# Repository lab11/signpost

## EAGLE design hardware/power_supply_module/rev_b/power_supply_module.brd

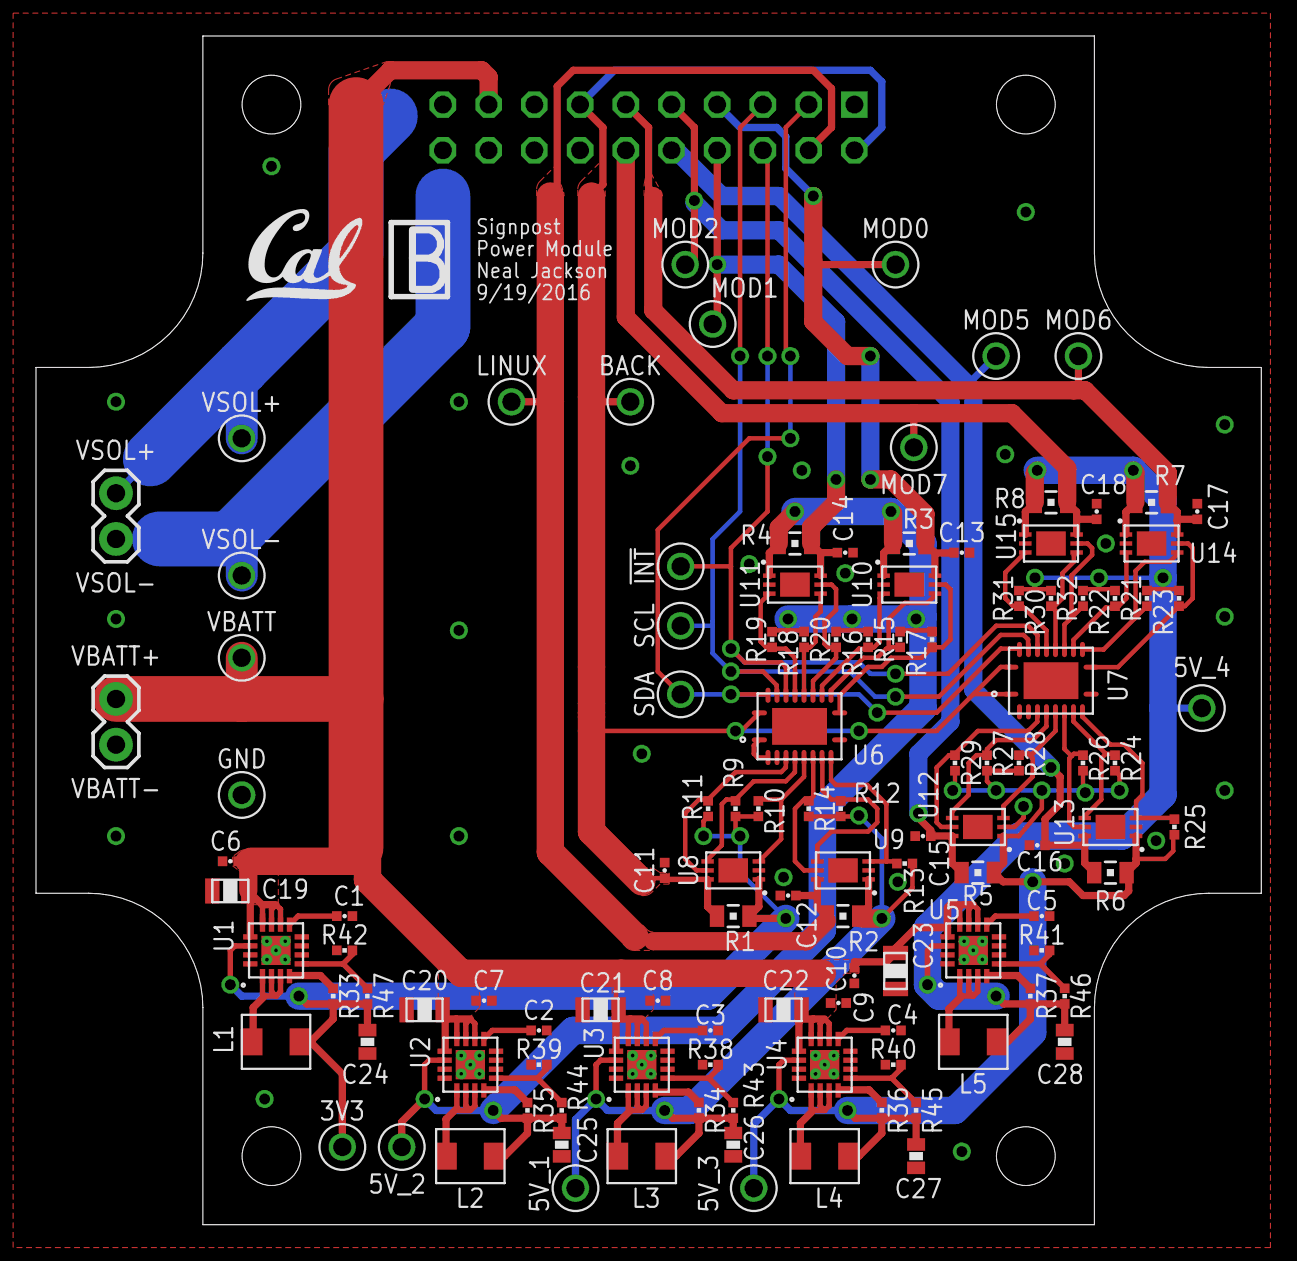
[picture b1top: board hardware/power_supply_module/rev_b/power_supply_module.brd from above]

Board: 2 copper layers, 68.1 x 66.0 mm, 119 parts (0 on the bottom side), 64 nets.

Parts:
3V3, 5V_1, 5V_2, 5V_3, 5V_4: TEST_POINT_0.040IN; TESTPOINT_0.040IN
!INT: TEST_POINT_0.040IN; TESTPOINT_0.040IN
BACK: TEST_POINT_0.040IN; TESTPOINT_0.040IN
C1, C2, C3, C4, C5: 3.3 nF; 0402_CAP
C6, C7, C8, C9, C10, C11, C12, C13, C14, C15, C16, C17, C18: 0.1 uF; 0402_CAP
C19, C20, C21, C22, C23: 10 uF; 0805_CAP
C24, C25, C26, C27, C28: 22 uF; 0603_CAP
GND: TEST_POINT_0.040IN; TESTPOINT_0.040IN
J1: MODULE_POWER
JP1, JP2: 1X02
L1, L2, L3, L4, L5: 2.2 uH; IHL-1212BZ-11
LINUX: TEST_POINT_0.040IN; TESTPOINT_0.040IN
MOD0, MOD1, MOD2, MOD5, MOD6, MOD7: TEST_POINT_0.040IN; TESTPOINT_0.040IN
R1, R2, R3, R4, R5, R6, R7, R8: 0.017 Ω; 0805_RES
R9, R10, R11, R12, R13, R14, R15, R16, R17, R18, R19, R20, R21, R22, R23, R24, R25, R26, R27, R28, R29, R30, R31, R32: 2 kΩ; 0402_RES
R33, R34, R35, R36, R37: 100 kΩ; 0402_RES
R38, R39, R40, R41: 130 kΩ; 0402_RES
R42: 240 kΩ; 0402_RES
R43, R44, R45, R46: 680 kΩ; 0402_RES
R47: 750 kΩ; 0402_RES
SCL: TEST_POINT_0.040IN; TESTPOINT_0.040IN
SDA: TEST_POINT_0.040IN; TESTPOINT_0.040IN
U1, U2, U3, U4, U5: TLV62130; TQFN-16/3MM
U6, U7: PCA9544AQFN-N20; QFN-N20
U8, U9, U10, U11, U12, U13, U14, U15: LTC2941; DFN-6-2MMX3MM
U$1: UCB_CAL_200MIL
VBATT: TEST_POINT_0.040IN; TESTPOINT_0.040IN
VSOL+: TEST_POINT_0.040IN; TESTPOINT_0.040IN
VSOL-: TEST_POINT_0.040IN; TESTPOINT_0.040IN

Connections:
3V3: 3V3.TESTPOINT, C24.2, L1.P$2, R1.2, R9.2, R10.2, R11.2, R33.2, R47.2, U1.14, U8.1
5V_1: 5V_1.TESTPOINT, C26.2, L3.P$2, R2.2, R12.2, R13.2, R14.2, R34.2, R43.2, U3.14, U9.1
5V_2: 5V_2.TESTPOINT, C25.2, L2.P$2, R3.2, R4.2, R15.2, R16.2, R17.2, R18.2, R19.2, R20.2, R35.2, R44.2, U2.14, U10.1, U11.1
5V_3: 5V_3.TESTPOINT, C27.2, L4.P$2, R5.2, R6.2, R24.2, R25.2, R26.2, R27.2, R28.2, R29.2, R36.2, R45.2, U4.14, U12.1, U13.1
5V_4: 5V_4.TESTPOINT, C28.2, L5.P$2, R7.2, R8.2, R21.2, R22.2, R23.2, R30.2, R31.2, R32.2, R37.2, R46.2, U5.14, U14.1, U15.1
!INT: !INT.TESTPOINT, J1.6, U6.17, U7.17
GND: C1.1, C2.1, C3.1, C4.1, C5.1, C6.2, C7.2, C8.2, C9.2, C10.2, C11.2, C12.2, C13.2, C14.2, C15.2, C16.2, C17.2, C18.2, C19.P$2, C20.P$2, C21.P$2, C22.P$2, C23.P$2, C24.1, C25.1, C26.1, C27.1, C28.1, GND.TESTPOINT, J1.1, J1.18, JP2.1, R38.1, R39.1, R40.1, R41.1, R42.1, U1.6, U1.7, U1.8, U1.15, U1.16, U1.GND, U2.6, U2.7, U2.8, U2.15, U2.16, U2.GND, U3.6, U3.7, U3.8, U3.15, U3.16, U3.GND, U4.6, U4.7, U4.8, U4.15, U4.16, U4.GND, U5.6, U5.7, U5.8, U5.15, U5.16, U5.GND, U6.1, U6.2, U6.3, U6.10, U7.2, U7.3, U7.10, U8.2, U9.2, U10.2, U11.2, U12.2, U13.2, U14.2, U15.2
unnamed: C2.2, U2.9
unnamed: L2.P$1, U2.1, U2.2, U2.3
unnamed: R35.1, U2.4
unnamed: R39.2, R44.1, U2.5
unnamed: C3.2, U3.9
unnamed: L3.P$1, U3.1, U3.2, U3.3
unnamed: R34.1, U3.4
unnamed: C4.2, U4.9
unnamed: R38.2, R43.1, U3.5
unnamed: L4.P$1, U4.1, U4.2, U4.3
unnamed: R36.1, U4.4
unnamed: R40.2, R45.1, U4.5
unnamed: C5.2, U5.9
unnamed: L5.P$1, U5.1, U5.2, U5.3
unnamed: R37.1, U5.4
unnamed: R41.2, R46.1, U5.5
unnamed: R27.1, U7.5, U12.4
unnamed: R28.1, U7.6, U12.3
unnamed: R21.1, U7.12, U14.4
unnamed: R22.1, U7.13, U14.3
unnamed: R23.1, U7.11, U14.5
unnamed: R30.1, U7.15, U15.4
unnamed: R31.1, U7.16, U15.3
unnamed: R9.1, U6.5, U8.4
unnamed: R32.1, U7.14, U15.5
unnamed: R10.1, U6.6, U8.3
unnamed: R29.1, U7.4, U12.5
unnamed: R24.1, U7.8, U13.4
unnamed: R25.1, U7.9, U13.3
unnamed: R26.1, U7.7, U13.5
unnamed: R15.1, U6.12, U10.4
unnamed: R16.1, U6.13, U10.3
unnamed: R17.1, U6.11, U10.5
unnamed: R18.1, U6.15, U11.4
unnamed: R19.1, U6.16, U11.3
unnamed: R20.1, U6.14, U11.5
unnamed: C1.2, U1.9
unnamed: L1.P$1, U1.1, U1.2, U1.3
unnamed: R33.1, U1.4
unnamed: R42.2, R47.1, U1.5
unnamed: R11.1, U6.4, U8.5
unnamed: R12.1, U6.8, U9.4
unnamed: R13.1, U6.9, U9.3
unnamed: R14.1, U6.7, U9.5
SCL: J1.5, SCL.TESTPOINT, U6.18, U7.18
SDA: J1.3, SDA.TESTPOINT, U6.19, U7.19
VBATT: C6.1, C7.1, C8.1, C9.1, C10.1, C19.P$1, C20.P$1, C21.P$1, C22.P$1, C23.P$1, J1.17, JP2.2, U1.10, U1.11, U1.12, U1.13, U2.10, U2.11, U2.12, U2.13, U3.10, U3.11, U3.12, U3.13, U4.10, U4.11, U4.12, U4.13, U5.10, U5.11, U5.12, U5.13, VBATT.TESTPOINT
VCC_BACKPLANE: BACK.TESTPOINT, C11.1, J1.2, J1.13, R1.1, U6.20, U7.1, U7.20, U8.6
VCC_LINUX: C12.1, J1.4, LINUX.TESTPOINT, R2.1, U9.6
VCC_MOD0: C13.1, J1.7, MOD0.TESTPOINT, R3.1, U10.6
VCC_MOD1: C14.1, J1.8, MOD1.TESTPOINT, R4.1, U11.6
VCC_MOD2: C15.1, J1.9, MOD2.TESTPOINT, R5.1, U12.6
VCC_MOD5: C16.1, J1.10, MOD5.TESTPOINT, R6.1, U13.6
VCC_MOD6: C17.1, J1.11, MOD6.TESTPOINT, R7.1, U14.6
VCC_MOD7: C18.1, J1.12, MOD7.TESTPOINT, R8.1, U15.6
VSOL+: J1.19, JP1.2, VSOL+.TESTPOINT
VSOL-: J1.20, JP1.1, VSOL-.TESTPOINT

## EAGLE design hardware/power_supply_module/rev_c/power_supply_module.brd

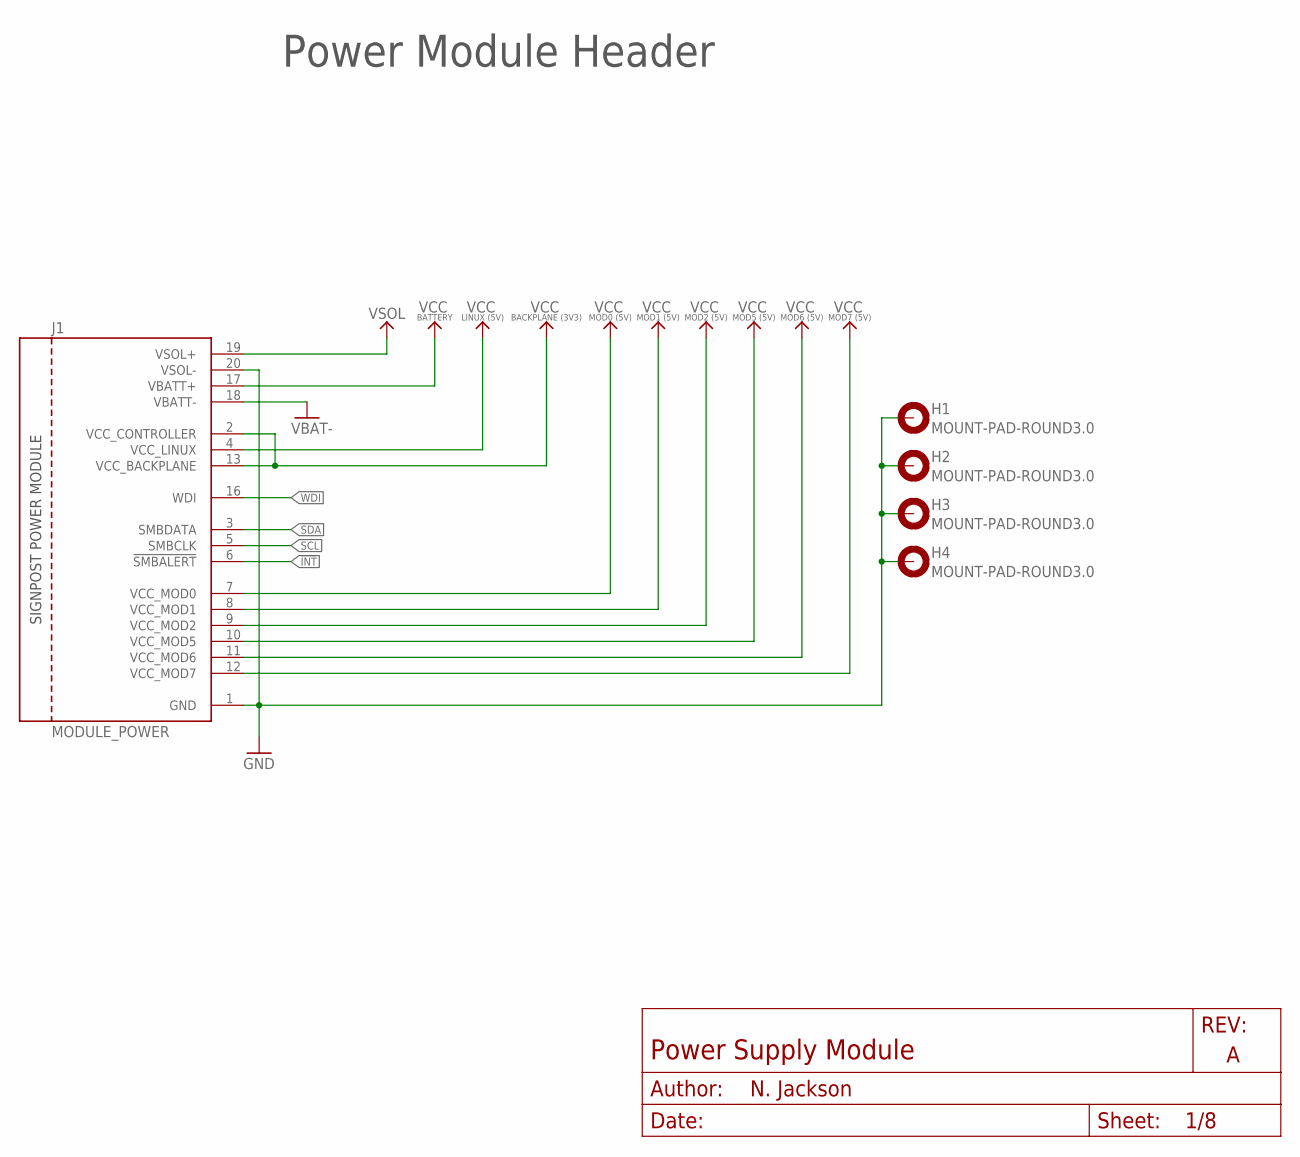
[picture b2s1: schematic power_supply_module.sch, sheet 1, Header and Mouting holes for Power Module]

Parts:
H1, H2, H3, H4: MOUNT-PAD-ROUND3.0; 3,0-PAD
J1: MODULE_POWER

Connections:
!INT: J1.6 (!SMBALERT); also elsewhere on the board
GND: H1.B3,0, H2.B3,0, H3.B3,0, H4.B3,0, J1.1 (GND), J1.20 (VSOL-); also elsewhere on the board
SCL: J1.5 (SMBCLK); also elsewhere on the board
SDA: J1.3 (SMBDATA); also elsewhere on the board
VBAT+: J1.17 (VBATT+); also elsewhere on the board
VBAT-: J1.18 (VBATT-); also elsewhere on the board
VCC_BACKPLANE: J1.2 (VCC_CONTROLLER), J1.13 (VCC_BACKPLANE); also elsewhere on the board
VCC_LINUX: J1.4 (VCC_LINUX); also elsewhere on the board
VCC_MOD0: J1.7 (VCC_MOD0); also elsewhere on the board
VCC_MOD1: J1.8 (VCC_MOD1); also elsewhere on the board
VCC_MOD2: J1.9 (VCC_MOD2); also elsewhere on the board
VCC_MOD5: J1.10 (VCC_MOD5); also elsewhere on the board
VCC_MOD6: J1.11 (VCC_MOD6); also elsewhere on the board
VCC_MOD7: J1.12 (VCC_MOD7); also elsewhere on the board
VSOL+: J1.19 (VSOL+); also elsewhere on the board
WDI: J1.16 (WDI); also elsewhere on the board

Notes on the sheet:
Power Module Header

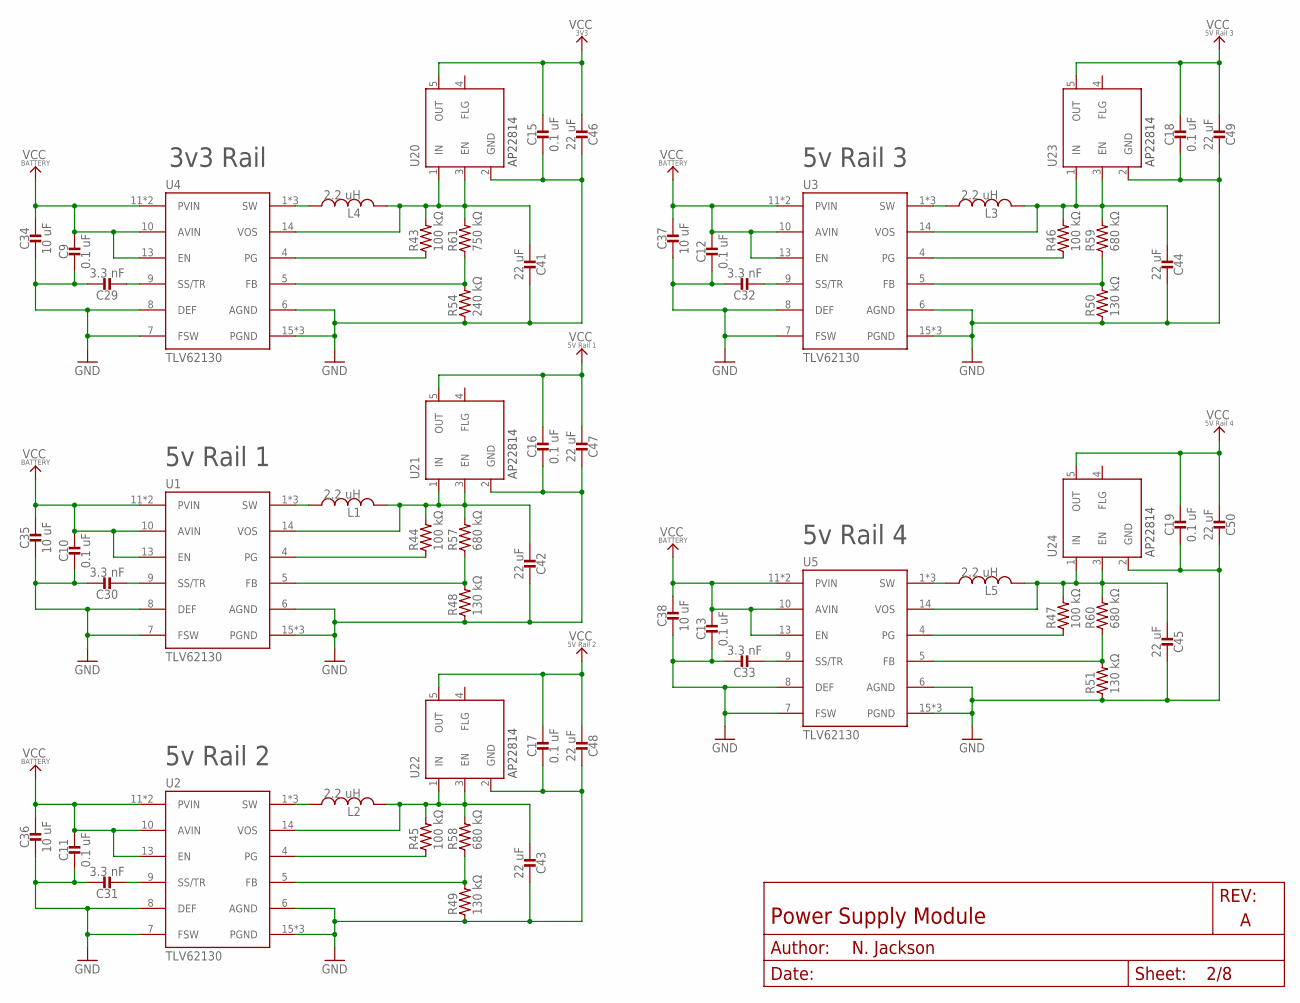
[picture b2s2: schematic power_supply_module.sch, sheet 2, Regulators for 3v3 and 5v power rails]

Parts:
C9, C10, C11, C12, C13, C15, C16, C17, C18, C19: 0.1 uF; 0402_CAP; DIGIKEY 490-5920-1-ND
C29, C30, C31, C32, C33: 3.3 nF; 0402_CAP; DIGIKEY 490-3248-1-ND
C34, C35, C36, C37, C38: 10 uF; 0805_CAP; DIGIKEY 490-5523-1-ND
C41, C42, C43, C44, C45, C46, C47, C48, C49, C50: 22 uF; 0603_CAP; DIGIKEY 1276-1193-1-ND
L1, L2, L3, L4, L5: 2.2 uH; IHL-1212BZ-11
R43, R44, R45, R46, R47: 100 kΩ; 0402_RES; DIGIKEY P100KJCT-ND
R48, R49, R50, R51: 130 kΩ; 0402_RES; DIGIKEY P130KLCT-ND
R54: 240 kΩ; 0402_RES; DIGIKEY P240JCT-ND
R57, R58, R59, R60: 680 kΩ; 0402_RES; DIGIKEY P680KLCT-ND
R61: 750 kΩ; 0402_RES; DIGIKEY P750KJCT-ND
U1, U2, U3, U4, U5: TLV62130; TQFN-16/3MM
U20, U21, U22, U23, U24: AP22814; U-DFN2020-6

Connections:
3V3ROUT: C41.2, L4.P$2 (2), R43.2, R61.2, U4.14 (VOS), U20.1 (IN), U20.3 (EN)
5V_1ROUT: C42.2, L1.P$2 (2), R44.2, R57.2, U1.14 (VOS), U21.1 (IN), U21.3 (EN)
5V_2ROUT: C43.2, L2.P$2 (2), R45.2, R58.2, U2.14 (VOS), U22.1 (IN), U22.3 (EN)
5V_3ROUT: C44.2, L3.P$2 (2), R46.2, R59.2, U3.14 (VOS), U23.1 (IN), U23.3 (EN)
5V_4ROUT: C45.2, L5.P$2 (2), R47.2, R60.2, U5.14 (VOS), U24.1 (IN), U24.3 (EN)
GND: C9.2, C10.2, C11.2, C12.2, C13.2, C15.2, C16.2, C17.2, C18.2, C19.2, C29.1, C30.1, C31.1, C32.1, C33.1, C34.P$2 (2), C35.P$2 (2), C36.P$2 (2), C37.P$2 (2), C38.P$2 (2), C41.1, C42.1, C43.1, C44.1, C45.1, C46.1, C47.1, C48.1, C49.1, C50.1, R48.1, R49.1, R50.1, R51.1, R54.1, U1.6 (AGND), U1.7 (FSW), U1.8 (DEF), U1.15 (PGND), U1.16 (PGND), U1.GND, U2.6 (AGND), U2.7 (FSW), U2.8 (DEF), U2.15 (PGND), U2.16 (PGND), U2.GND, U3.6 (AGND), U3.7 (FSW), U3.8 (DEF), U3.15 (PGND), U3.16 (PGND), U3.GND, U4.6 (AGND), U4.7 (FSW), U4.8 (DEF), U4.15 (PGND), U4.16 (PGND), U4.GND, U5.6 (AGND), U5.7 (FSW), U5.8 (DEF), U5.15 (PGND), U5.16 (PGND), U5.GND, U20.2 (GND), U21.2 (GND), U22.2 (GND), U23.2 (GND), U24.2 (GND); also elsewhere on the board
unnamed: L4.P$1 (1), U4.1 (SW), U4.2 (SW), U4.3 (SW)
unnamed: C30.2, U1.9 (SS/TR)
unnamed: R44.1, U1.4 (PG)
unnamed: R48.2, R57.1, U1.5 (FB)
unnamed: C31.2, U2.9 (SS/TR)
unnamed: L2.P$1 (1), U2.1 (SW), U2.2 (SW), U2.3 (SW)
unnamed: R45.1, U2.4 (PG)
unnamed: R49.2, R58.1, U2.5 (FB)
unnamed: C29.2, U4.9 (SS/TR)
unnamed: L1.P$1 (1), U1.1 (SW), U1.2 (SW), U1.3 (SW)
unnamed: C32.2, U3.9 (SS/TR)
unnamed: R43.1, U4.4 (PG)
unnamed: R54.2, R61.1, U4.5 (FB)
unnamed: L3.P$1 (1), U3.1 (SW), U3.2 (SW), U3.3 (SW)
unnamed: R46.1, U3.4 (PG)
unnamed: R50.2, R59.1, U3.5 (FB)
unnamed: C33.2, U5.9 (SS/TR)
unnamed: L5.P$1 (1), U5.1 (SW), U5.2 (SW), U5.3 (SW)
unnamed: R47.1, U5.4 (PG)
unnamed: R51.2, R60.1, U5.5 (FB)
VBAT+: C9.1, C10.1, C11.1, C12.1, C13.1, C34.P$1 (1), C35.P$1 (1), C36.P$1 (1), C37.P$1 (1), C38.P$1 (1), U1.10 (AVIN), U1.11 (PVIN), U1.12 (PVIN), U1.13 (EN), U2.10 (AVIN), U2.11 (PVIN), U2.12 (PVIN), U2.13 (EN), U3.10 (AVIN), U3.11 (PVIN), U3.12 (PVIN), U3.13 (EN), U4.10 (AVIN), U4.11 (PVIN), U4.12 (PVIN), U4.13 (EN), U5.10 (AVIN), U5.11 (PVIN), U5.12 (PVIN), U5.13 (EN); also elsewhere on the board
VCC_3V3: C15.1, C46.2, U20.5 (OUT); also elsewhere on the board
VCC_5V_1: C16.1, C47.2, U21.5 (OUT); also elsewhere on the board
VCC_5V_2: C17.1, C48.2, U22.5 (OUT); also elsewhere on the board
VCC_5V_3: C18.1, C49.2, U23.5 (OUT); also elsewhere on the board
VCC_5V_4: C19.1, C50.2, U24.5 (OUT); also elsewhere on the board

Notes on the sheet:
3v3 Rail
5v Rail 1
5v Rail 2
5v Rail 4
5v Rail 3

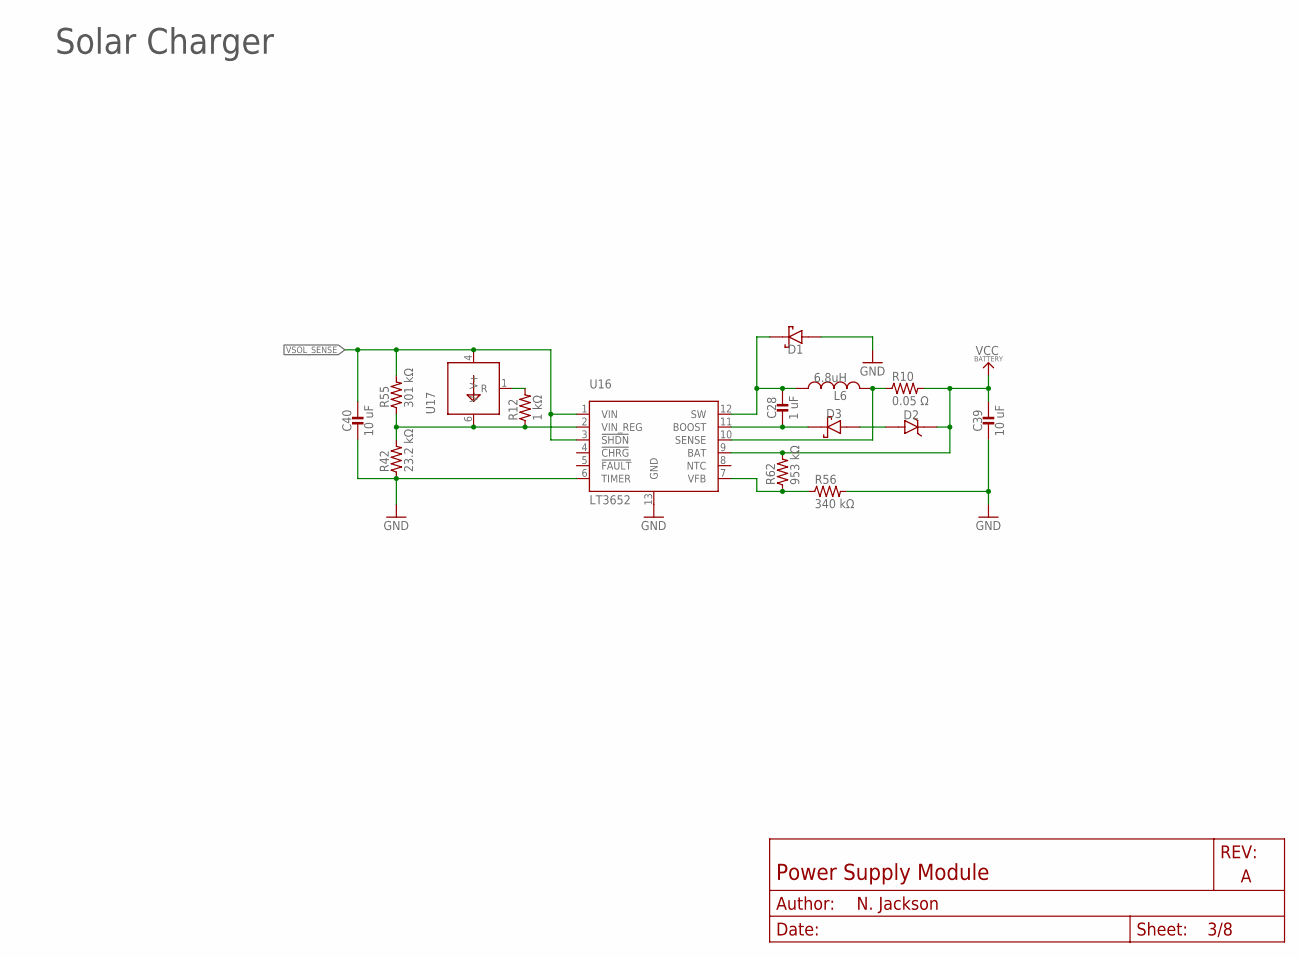
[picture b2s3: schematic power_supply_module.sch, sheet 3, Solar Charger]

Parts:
C28: 1 uF; 0603_CAP; DIGIKEY 490-3890-1-ND
C39, C40: 10 uF; 0805_CAP; DIGIKEY 490-5523-1-ND
D1: DIODE_SCHOTTKYSOT-23F; SOT-23F; DIGIKEY CMPSH1-4 CT-ND
D2: DIODE_ZENERSOT323; SOD323; DIGIKEY 1727-5151-1-ND
D3: DIODE_SCHOTTKYSOT-23F; SOT-23F; DIGIKEY CMDSH2-4L CT-ND
L6: 6.8uH; IHL-2525CZ; DIGIKEY 541-2582-1-ND
R10: 0.05 Ω; 0805_RES; DIGIKEY WSLPB-.05CT-ND
R12: 1 kΩ; 0402_RES; DIGIKEY P1.0KJCT-ND
R42: 23.2 kΩ; 0402_RES; DIGIKEY 311-2257-1-ND
R55: 301 kΩ; 0402_RES; DIGIKEY P301KLCT-ND
R56: 340 kΩ; 0402_RES; DIGIKEY P340KLCT-ND
R62: 953 kΩ; 0402_RES; DIGIKEY P953KLCT-ND
U16: LT3652; DFN-12/3MM
U17: LM234; SOIC-8

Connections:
BOOST: C28.2, D3.P$3 (CATHODE), U16.11 (BOOST)
GND: C39.P$2 (2), C40.P$2 (2), D1.P$1 (ANODE), R42.1, R56.2, U16.6 (TIMER), U16.13 (GND); also elsewhere on the board
unnamed: D2.P$2 (ANODE), D3.P$1 (ANODE)
unnamed: R12.2, U17.1 (R)
SENSE: L6.P$2 (2), R10.1, U16.10 (SENSE)
SW: C28.1, D1.P$3 (CATHODE), L6.P$1 (1), U16.12 (SW)
VBAT+: C39.P$1 (1), D2.P$1 (CATHODE), R10.2, R62.2, U16.9 (BAT); also elsewhere on the board
VFB: R56.1, R62.1, U16.7 (VFB)
VINREG: R12.1, R42.2, R55.1, U16.2 (VIN_REG), U17.6 (V-)
VSOL_SENSE: C40.P$1 (1), R55.2, U16.1 (VIN), U16.3 (!SHDN), U17.4 (V+); also elsewhere on the board

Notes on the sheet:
Solar Charger

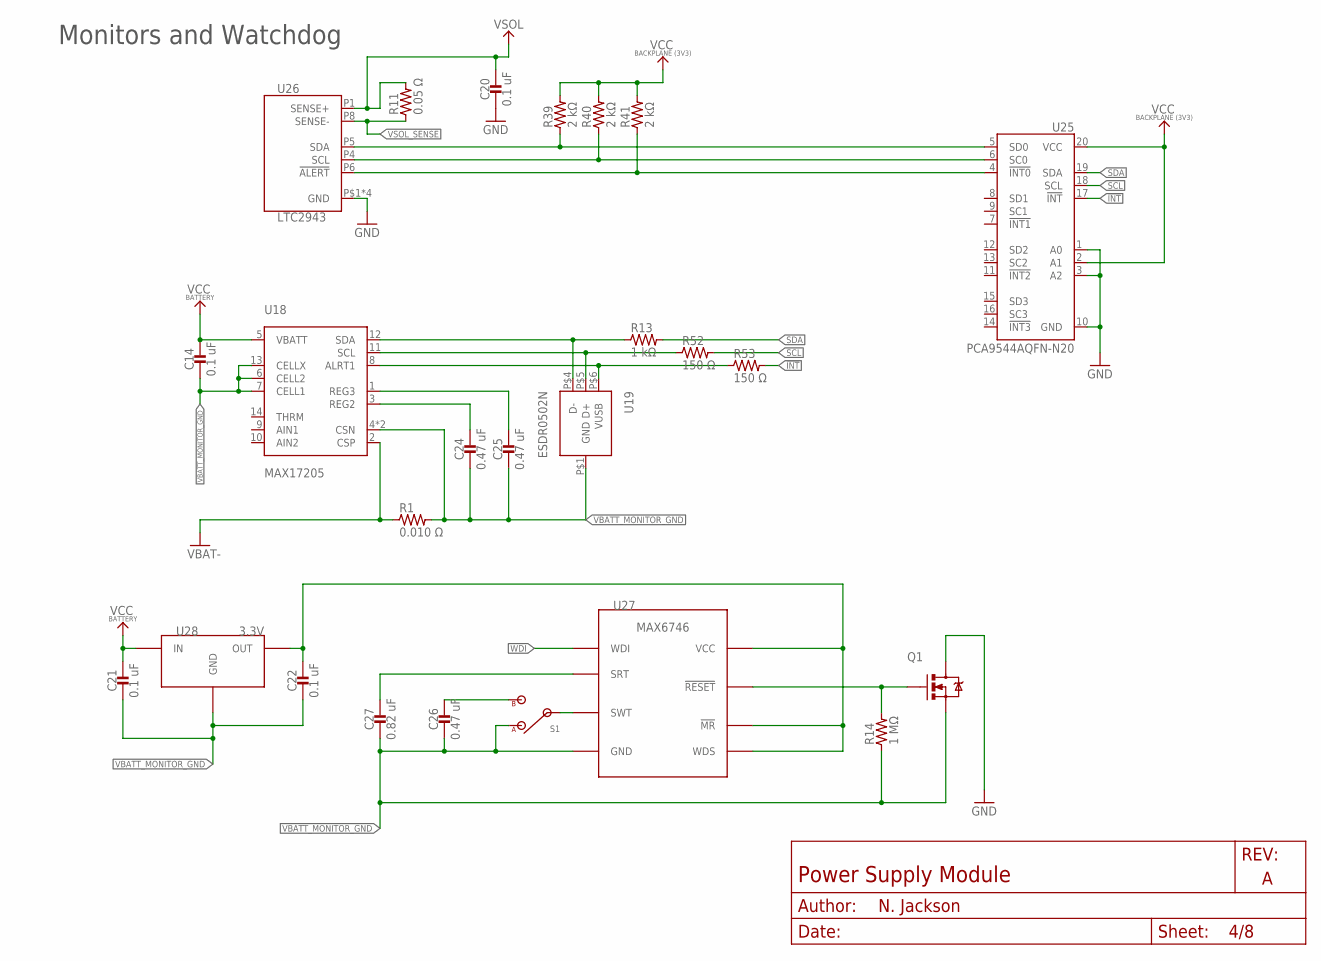
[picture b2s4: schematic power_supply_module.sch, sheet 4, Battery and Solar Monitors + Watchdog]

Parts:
C14, C20, C21, C22: 0.1 uF; 0402_CAP; DIGIKEY 490-5920-1-ND
C24, C25, C26: 0.47 uF; 0402_CAP; DIGIKEY 490-3266-1-ND
C27: 0.82 uF; 0402_CAP; DIGIKEY 490-10440-1-ND
Q1: MOSFET-NCHANNELFDD8580; DPAK; DIGIKEY NTD4965NT4GOSCT-ND
R1: 0.010 Ω; 0805_RES; DIGIKEY WSLPB-.01CT-ND
R11: 0.05 Ω; 0805_RES; DIGIKEY WSLPB-.05CT-ND
R13: 1 kΩ; 0402_RES; DIGIKEY P1.0KJCT-ND
R14: 1 MΩ; 0402_RES; DIGIKEY P1.00MLCT-ND
R39, R40, R41: 2 kΩ; 0402_RES; DIGIKEY P2.00KLCT-ND
R52, R53: 150 Ω; 0402_RES; DIGIKEY P150LCT-ND
S1: TE_SSA12/SPDT
U18: MAX17205; 14-TDFN
U19: ESDR0502N; UDFN-6
U25: PCA9544AQFN-N20; QFN-N20
U26: LTC2943; DFN-8
U27: MAX6746; SOT-23-8
U28: 3.3V; SOT-23

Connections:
!INT: R53.2, U25.17 (!INT); also elsewhere on the board
GND: C20.2, Q1.4 (D), U25.1 (A0), U25.3 (A2), U25.10 (GND), U26.P2 (GND), U26.P3 (GND), U26.P7 (GND), U26.P$1 (GND); also elsewhere on the board
unnamed: C27.1, U27.3 (SRT)
unnamed: R13.1, U18.12 (SDA), U19.P$4 (D-)
unnamed: C26.1, S1.2 (B)
unnamed: R52.1, U18.11 (SCL), U19.P$5 (D+)
unnamed: C24.1, U18.3 (REG2)
unnamed: R53.1, U18.8 (ALRT1), U19.P$6 (VUSB)
unnamed: C25.1, U18.1 (REG3)
unnamed: S1.IN, U27.2 (SWT)
unnamed: Q1.1 (G), R14.2, U27.7 (!RESET)
unnamed: C22.1, U27.1 (!MR), U27.5 (WDS), U27.8 (VCC), U28.1 (OUT)
unnamed: R41.1, U25.4 (!INT0), U26.P6 (!ALERT)
unnamed: R40.1, U25.6 (SC0), U26.P4 (SCL)
unnamed: R39.1, U25.5 (SD0), U26.P5 (SDA)
SCL: R52.2, U25.18 (SCL); also elsewhere on the board
SDA: R13.2, U25.19 (SDA); also elsewhere on the board
VBAT+: C14.1, C21.1, U18.5 (VBATT), U28.2 (IN); also elsewhere on the board
VBAT-: R1.1, U18.2 (CSP); also elsewhere on the board
VBATT_MONITOR_GND: C14.2, C21.2, C22.2, C24.2, C25.2, C26.2, C27.2, Q1.3 (S), R1.2, R14.1, S1.1 (A), U18.4 (CSN), U18.6 (CELL2), U18.7 (CELL1), U18.13 (CELLX), U18.15 (CSN), U19.P$1 (GND), U27.4 (GND), U28.3 (GND); also elsewhere on the board
VCC_BACKPLANE: R39.2, R40.2, R41.2, U25.2 (A1), U25.20 (VCC); also elsewhere on the board
VSOL+: C20.1, R11.2, U26.P1 (SENSE+); also elsewhere on the board
VSOL_SENSE: R11.1, U26.P8 (SENSE-); also elsewhere on the board
WDI: U27.6 (WDI); also elsewhere on the board

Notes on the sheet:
Monitors and Watchdog

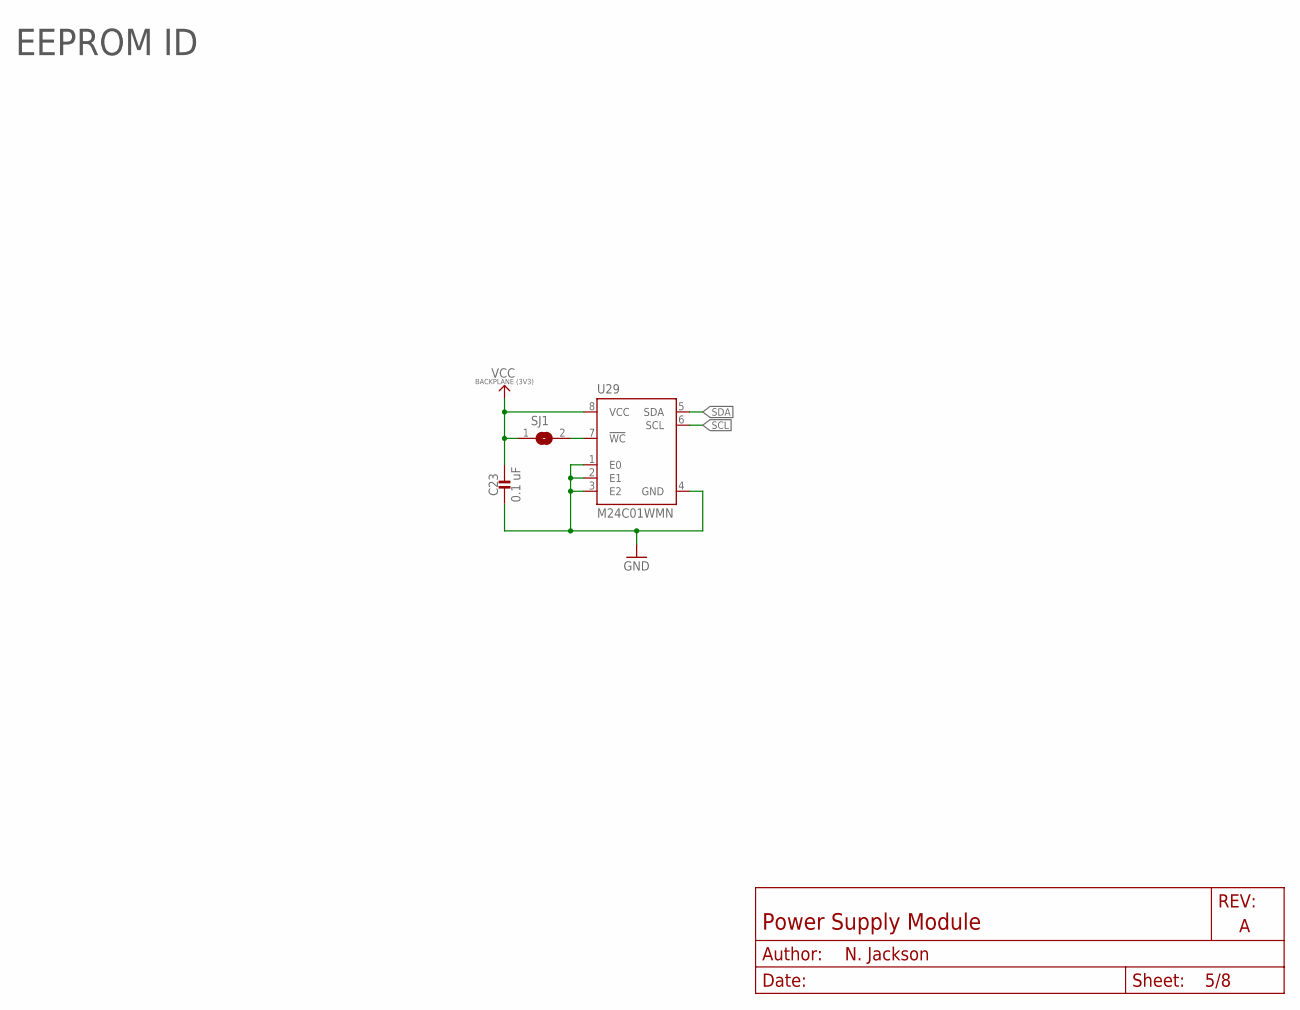
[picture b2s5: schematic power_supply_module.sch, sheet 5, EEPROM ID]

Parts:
C23: 0.1 uF; 0402_CAP; DIGIKEY 490-5920-1-ND
SJ1: SJ
U29: M24C01WMN; SOIC-8

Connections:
GND: C23.2, U29.1 (E0), U29.2 (E1), U29.3 (E2), U29.4 (GND); also elsewhere on the board
unnamed: SJ1.2, U29.7 (!WC)
SCL: U29.6 (SCL); also elsewhere on the board
SDA: U29.5 (SDA); also elsewhere on the board
VCC_BACKPLANE: C23.1, SJ1.1, U29.8 (VCC); also elsewhere on the board

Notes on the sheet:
EEPROM ID

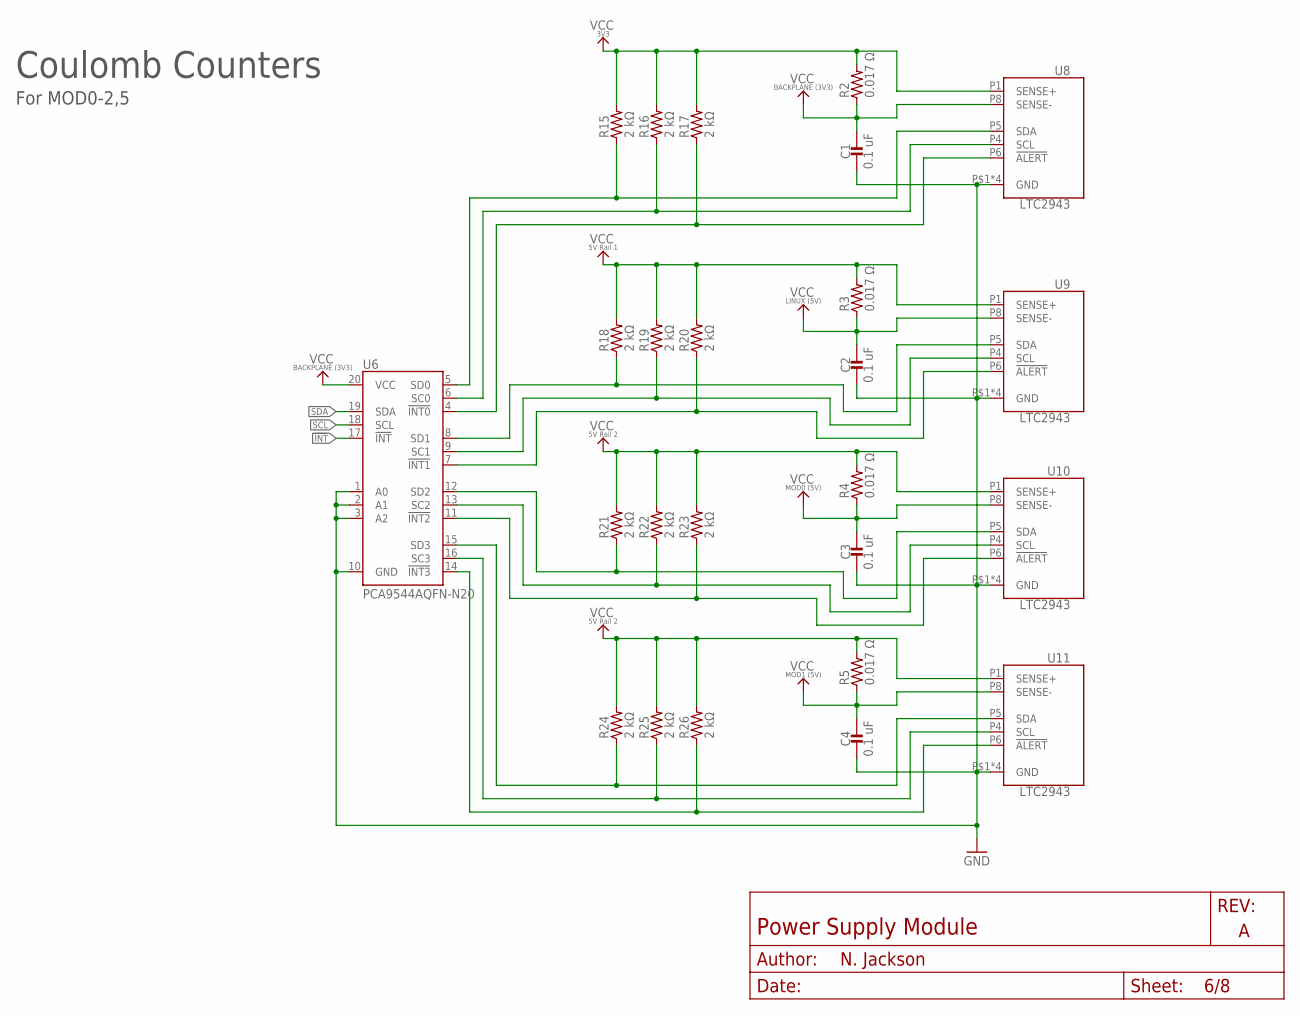
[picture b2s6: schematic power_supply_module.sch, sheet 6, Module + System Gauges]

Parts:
C1, C2, C3, C4: 0.1 uF; 0402_CAP; DIGIKEY 490-5920-1-ND
R2, R3, R4, R5: 0.017 Ω; 0805_RES; DIGIKEY WSLPB-.017CT-ND
R15, R16, R17, R18, R19, R20, R21, R22, R23, R24, R25, R26: 2 kΩ; 0402_RES; DIGIKEY P2.00KLCT-ND
U6: PCA9544AQFN-N20; QFN-N20
U8, U9, U10, U11: LTC2943; DFN-8

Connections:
!INT: U6.17 (!INT); also elsewhere on the board
GND: C1.2, C2.2, C3.2, C4.2, U6.1 (A0), U6.2 (A1), U6.3 (A2), U6.10 (GND), U8.P2 (GND), U8.P3 (GND), U8.P7 (GND), U8.P$1 (GND), U9.P2 (GND), U9.P3 (GND), U9.P7 (GND), U9.P$1 (GND), U10.P2 (GND), U10.P3 (GND), U10.P7 (GND), U10.P$1 (GND), U11.P2 (GND), U11.P3 (GND), U11.P7 (GND), U11.P$1 (GND); also elsewhere on the board
unnamed: R15.1, U6.5 (SD0), U8.P5 (SDA)
unnamed: R16.1, U6.6 (SC0), U8.P4 (SCL)
unnamed: R21.1, U6.12 (SD2), U10.P5 (SDA)
unnamed: R22.1, U6.13 (SC2), U10.P4 (SCL)
unnamed: R23.1, U6.11 (!INT2), U10.P6 (!ALERT)
unnamed: R24.1, U6.15 (SD3), U11.P5 (SDA)
unnamed: R25.1, U6.16 (SC3), U11.P4 (SCL)
unnamed: R26.1, U6.14 (!INT3), U11.P6 (!ALERT)
unnamed: R17.1, U6.4 (!INT0), U8.P6 (!ALERT)
unnamed: R18.1, U6.8 (SD1), U9.P5 (SDA)
unnamed: R19.1, U6.9 (SC1), U9.P4 (SCL)
unnamed: R20.1, U6.7 (!INT1), U9.P6 (!ALERT)
SCL: U6.18 (SCL); also elsewhere on the board
SDA: U6.19 (SDA); also elsewhere on the board
VCC_3V3: R2.2, R15.2, R16.2, R17.2, U8.P1 (SENSE+); also elsewhere on the board
VCC_5V_1: R3.2, R18.2, R19.2, R20.2, U9.P1 (SENSE+); also elsewhere on the board
VCC_5V_2: R4.2, R5.2, R21.2, R22.2, R23.2, R24.2, R25.2, R26.2, U10.P1 (SENSE+), U11.P1 (SENSE+); also elsewhere on the board
VCC_BACKPLANE: C1.1, R2.1, U6.20 (VCC), U8.P8 (SENSE-); also elsewhere on the board
VCC_LINUX: C2.1, R3.1, U9.P8 (SENSE-); also elsewhere on the board
VCC_MOD0: C3.1, R4.1, U10.P8 (SENSE-); also elsewhere on the board
VCC_MOD1: C4.1, R5.1, U11.P8 (SENSE-); also elsewhere on the board

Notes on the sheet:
Coulomb Counters
For MOD0-2,5

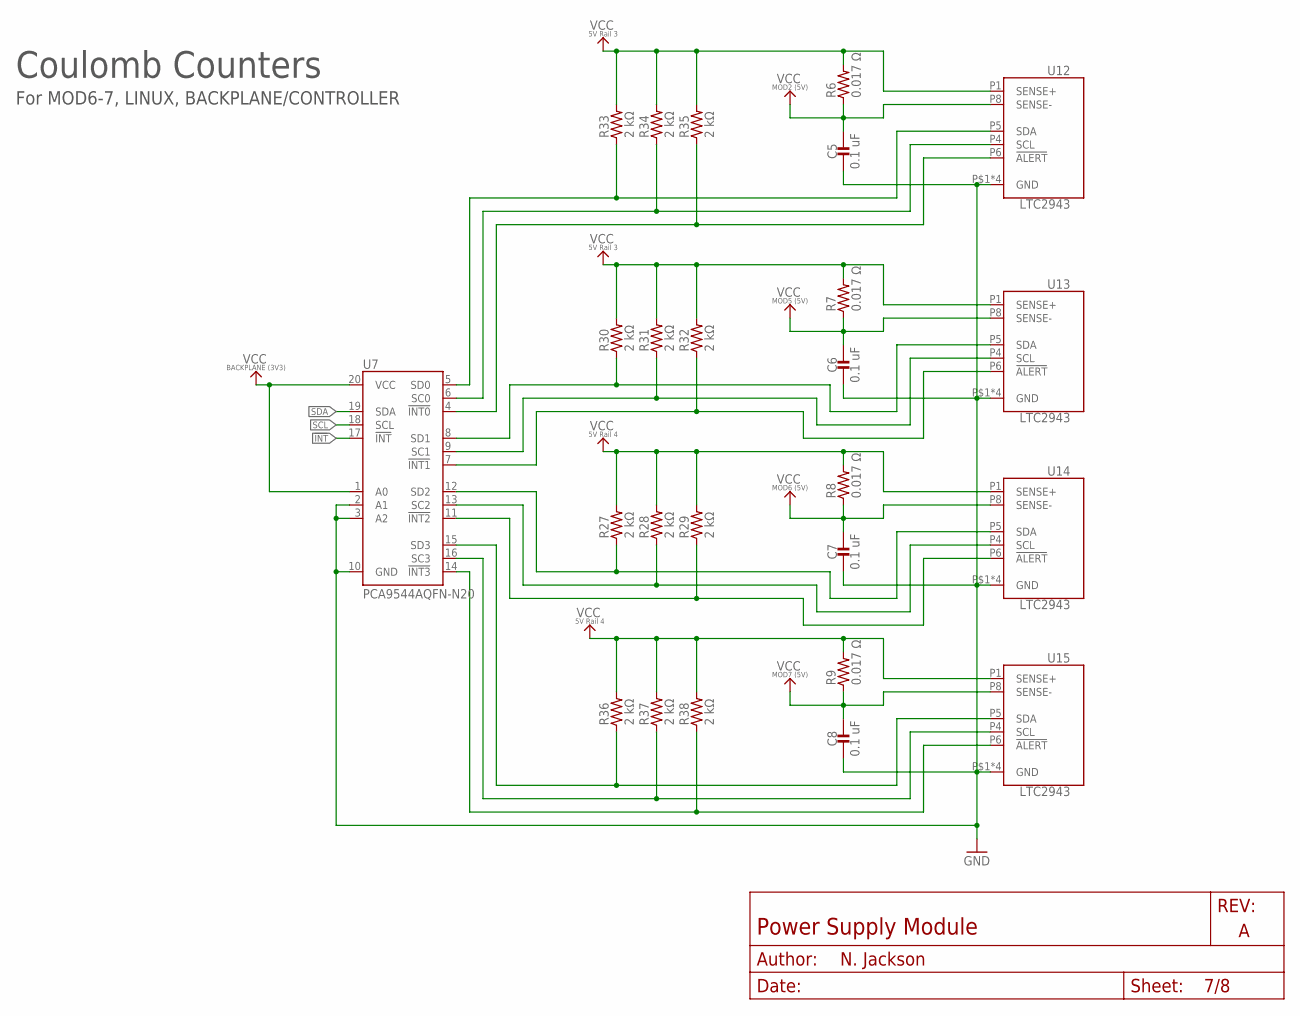
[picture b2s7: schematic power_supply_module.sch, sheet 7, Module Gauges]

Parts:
C5, C6, C7, C8: 0.1 uF; 0402_CAP; DIGIKEY 490-5920-1-ND
R6, R7, R8, R9: 0.017 Ω; 0805_RES; DIGIKEY WSLPB-.017CT-ND
R27, R28, R29, R30, R31, R32, R33, R34, R35, R36, R37, R38: 2 kΩ; 0402_RES; DIGIKEY P2.00KLCT-ND
U7: PCA9544AQFN-N20; QFN-N20
U12, U13, U14, U15: LTC2943; DFN-8

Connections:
!INT: U7.17 (!INT); also elsewhere on the board
GND: C5.2, C6.2, C7.2, C8.2, U7.2 (A1), U7.3 (A2), U7.10 (GND), U12.P2 (GND), U12.P3 (GND), U12.P7 (GND), U12.P$1 (GND), U13.P2 (GND), U13.P3 (GND), U13.P7 (GND), U13.P$1 (GND), U14.P2 (GND), U14.P3 (GND), U14.P7 (GND), U14.P$1 (GND), U15.P2 (GND), U15.P3 (GND), U15.P7 (GND), U15.P$1 (GND); also elsewhere on the board
unnamed: R33.1, U7.5 (SD0), U12.P5 (SDA)
unnamed: R34.1, U7.6 (SC0), U12.P4 (SCL)
unnamed: R27.1, U7.12 (SD2), U14.P5 (SDA)
unnamed: R28.1, U7.13 (SC2), U14.P4 (SCL)
unnamed: R29.1, U7.11 (!INT2), U14.P6 (!ALERT)
unnamed: R36.1, U7.15 (SD3), U15.P5 (SDA)
unnamed: R37.1, U7.16 (SC3), U15.P4 (SCL)
unnamed: R38.1, U7.14 (!INT3), U15.P6 (!ALERT)
unnamed: R35.1, U7.4 (!INT0), U12.P6 (!ALERT)
unnamed: R30.1, U7.8 (SD1), U13.P5 (SDA)
unnamed: R31.1, U7.9 (SC1), U13.P4 (SCL)
unnamed: R32.1, U7.7 (!INT1), U13.P6 (!ALERT)
SCL: U7.18 (SCL); also elsewhere on the board
SDA: U7.19 (SDA); also elsewhere on the board
VCC_5V_3: R6.2, R7.2, R30.2, R31.2, R32.2, R33.2, R34.2, R35.2, U12.P1 (SENSE+), U13.P1 (SENSE+); also elsewhere on the board
VCC_5V_4: R8.2, R9.2, R27.2, R28.2, R29.2, R36.2, R37.2, R38.2, U14.P1 (SENSE+), U15.P1 (SENSE+); also elsewhere on the board
VCC_BACKPLANE: U7.1 (A0), U7.20 (VCC); also elsewhere on the board
VCC_MOD2: C5.1, R6.1, U12.P8 (SENSE-); also elsewhere on the board
VCC_MOD5: C6.1, R7.1, U13.P8 (SENSE-); also elsewhere on the board
VCC_MOD6: C7.1, R8.1, U14.P8 (SENSE-); also elsewhere on the board
VCC_MOD7: C8.1, R9.1, U15.P8 (SENSE-); also elsewhere on the board

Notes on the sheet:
Coulomb Counters
For MOD6-7, LINUX, BACKPLANE/CONTROLLER

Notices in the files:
parts and their libraries:
SparkFun-Connectors: Licensing: CC v3.0 Share-Alike You are welcome to use this library for commercial purposes.
